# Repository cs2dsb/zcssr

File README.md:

# ZCSSR - Zero crossing solid state relay controller

A PCB and software for a SSR controller that monitors mains AC zero crossings to determine when to turn the SSR on.

[more images](docs/img)

## Why

I wanted to build a spot welder from an old MOT (microwave oven transformer) but wasn't satisfied with simply enabling the SSR at random because this makes the pulse +/- 1 half mains cycle (10ms on 50Hz, 8.3ms on 60Hz). It probably doesn't make much difference in the grand scheme of things but I wanted to know exactly how long the pulses were. 

This controller solves that issue by monitoring the mains zero crossing and triggering the SSR just before a zero crossing - the SSR has it's own zero crossing circuit to actually turn on it's output so as long as the controller doesn't fire more than 1 cycle early it will work as expected.

I also wanted to completely finish an embedded project written in rust and this project seemed about the right size undertaking.

## Uses

* Spot welder
* Reflow oven
* Sous vide
* Smoker
* Probably other things that need temp input (K-Type thermocouple) and switched mains ouput

## Features

* Zero crossing detection circuit
  * Pulse at least 0.4ms before the zero crossing
  * Isolated
  * 100-240V, 50/60Hz
  * [Details](docs/SimpleIsolatedZeroCrossDetector.pdf)
* UI
  * Quadrature encoder with push button 
  * LED for general status
  * LED for SSR status
  * 4 digit 14-segment LCD display. I2C
  * Trigger input 
* Temperature monitoring
  * NTC thermister for monitoring SSR/Transformer temperature
  * K-Type thermocouple input. MAX31855
* STM32F1 64-pin LQFP MCU. Specifically STM32F103RCT but any should work
* SWD (serial wire debug) programming & debugging
* USB hardware. In theory USB programming will be possible but not yet implemented

## Tools used

Not a complete list. Will add to it as features get implemented

* [Kicad](http://www.kicad.org/)
* [Rust](http://www.rust-lang.org/)
  * [cortex-m](http://github.com/rust-embedded/cortex-m) and [cortex-m-rt](http://github.com/rust-embedded/cortex-m-rt)
  * [cortex-m-rtfm RTOS](http://github.com/rtfm-rs/cortex-m-rtfm)
  * [stm32-rs peripheral register definitions](http://github.com/stm32-rs/stm32-rs)
  * [stm32f1xx-hal HAL implementation](http://github.com/stm32-rs/stm32f1xx-hal)
  * [adafruit-alphanum4.rs driver for Adafruit 14-segment LED Alphanumeric Backpack](http://github.com/cs2dsb/adafruit-alphanum4.rs)
    * [ht16k33 LED driver](http://github.com/jasonpeacock/ht16k33)

## Documentation

### Getting started

* Clone the repo
* Run `./bootstrap` script which will:
  * Initialize git submodules
  * Run `firmware/bootstrap` which will:
    * Checks if OS dependencies are installed
      * Currently `gcc`, `gdb`, `openocd` and `libudev-dev`
      * `sudo firmware/install_apt_deps` will install these deps if you are using a distribution that uses `apt`
    * Install or update rustup
    * Install required rust embedded toolchains
    * Install utils from crates.io
      * cargo-binutils
      * cargo-watch
      * llvm-tools-preview
      * serialitm
    * Run a cargo check, build and doc of the firmware (will take quite a while the first time)
* Direct flashing the the device
  * `firmware/deploy_standalone` will start openocd, flash the program and restart the device
* Debugging with gdb
  * `firmware/run_openocd` in one terminal
  * `firmware/release` or `firmware/debug` to build and launch gdb
  * Take a look at `firmware/openocd.gdb` and the scripts above to tweak the behaviour
* Log output
  * Firmware built with `--feature itm` will log over SWD
  * `firmware/monitor_itm` will launch `serialitm` to print this output with the ITM control characters stripped out. You may need to tweak the script if your uart dongle isn't `/dev/ttyUSB0`
* Tmux
  * `firmware/tmux_workspace` is a script that will open a tmux session with `firmware/run_openocd`, `firmware/monitor_itm` and `firmware/watch` in differnt panes to make development easy. Just type `./release` in one of the spare panes to deploy the software with gdb

### ITM logging

The code uses ITM logging to indicate start up progress and log info like temperatures and user config. If the ITM feature is enabled, the microcontroller won't run without openocd connected because there is some debug config openocd does to the chip that makes ITM work. I've added the obvious checks to the [itm_logger](https://github.com/cs2dsb/itm_logger.rs) crate but there's still something missing that I haven't got to the bottom of yet. There's [an issue](https://github.com/cs2dsb/itm_logger.rs/issues/1) to track it. The bottom line is if you want to be able to plug the hardware into the mains without OpenOCD connected you need to disable the `itm` feature (`firmware/deploy_standalone` already does this.)

### More info

Check [the docs folder](docs) for information on setting up the dev environment and various info on making the hardware.

## Mains warning

* Mains is dangerous, see the disclaimer
* A specific issue you might hit is powering the device over USB during development then plugging the mains in while the USB dongle is still attached. The mains will power the AC/DC on the board and that will backfeed 5v into the 3.3v/5v provided by the dongle. It's fine to leave the dongle connected if you disconnect it's 3.3v/5v line - only ground, swd, swclk should be connected to the ST-LINK if you want to plug the mains in. The UART connected to ground and swo is also fine. If you do backfeed 5v to the ST-LINK expect the ST-LINK to break as a minimum and the USB port it's connected to as a worst case. 

## Disclaimer

* This project uses mains electricity and will kill you if you handle it improperly
* You are responsible for your own safety
* Despite best efforts the author makes no guarantees that this design is safe, fit for purpose or meets any quality standards
* If you decide to build this or a similar device you must understand and take necessary safety precautions before proceeding
* The author cannot be held responsible for any damages or any form of loss that comes as a result of using any information found in this project

## License

This template is licensed under either of

- Apache License, Version 2.0 ([LICENSE-APACHE](LICENSE-APACHE) or
  http://www.apache.org/licenses/LICENSE-2.0)

- MIT license ([LICENSE-MIT](LICENSE-MIT) or http://opensource.org/licenses/MIT)

at your option.

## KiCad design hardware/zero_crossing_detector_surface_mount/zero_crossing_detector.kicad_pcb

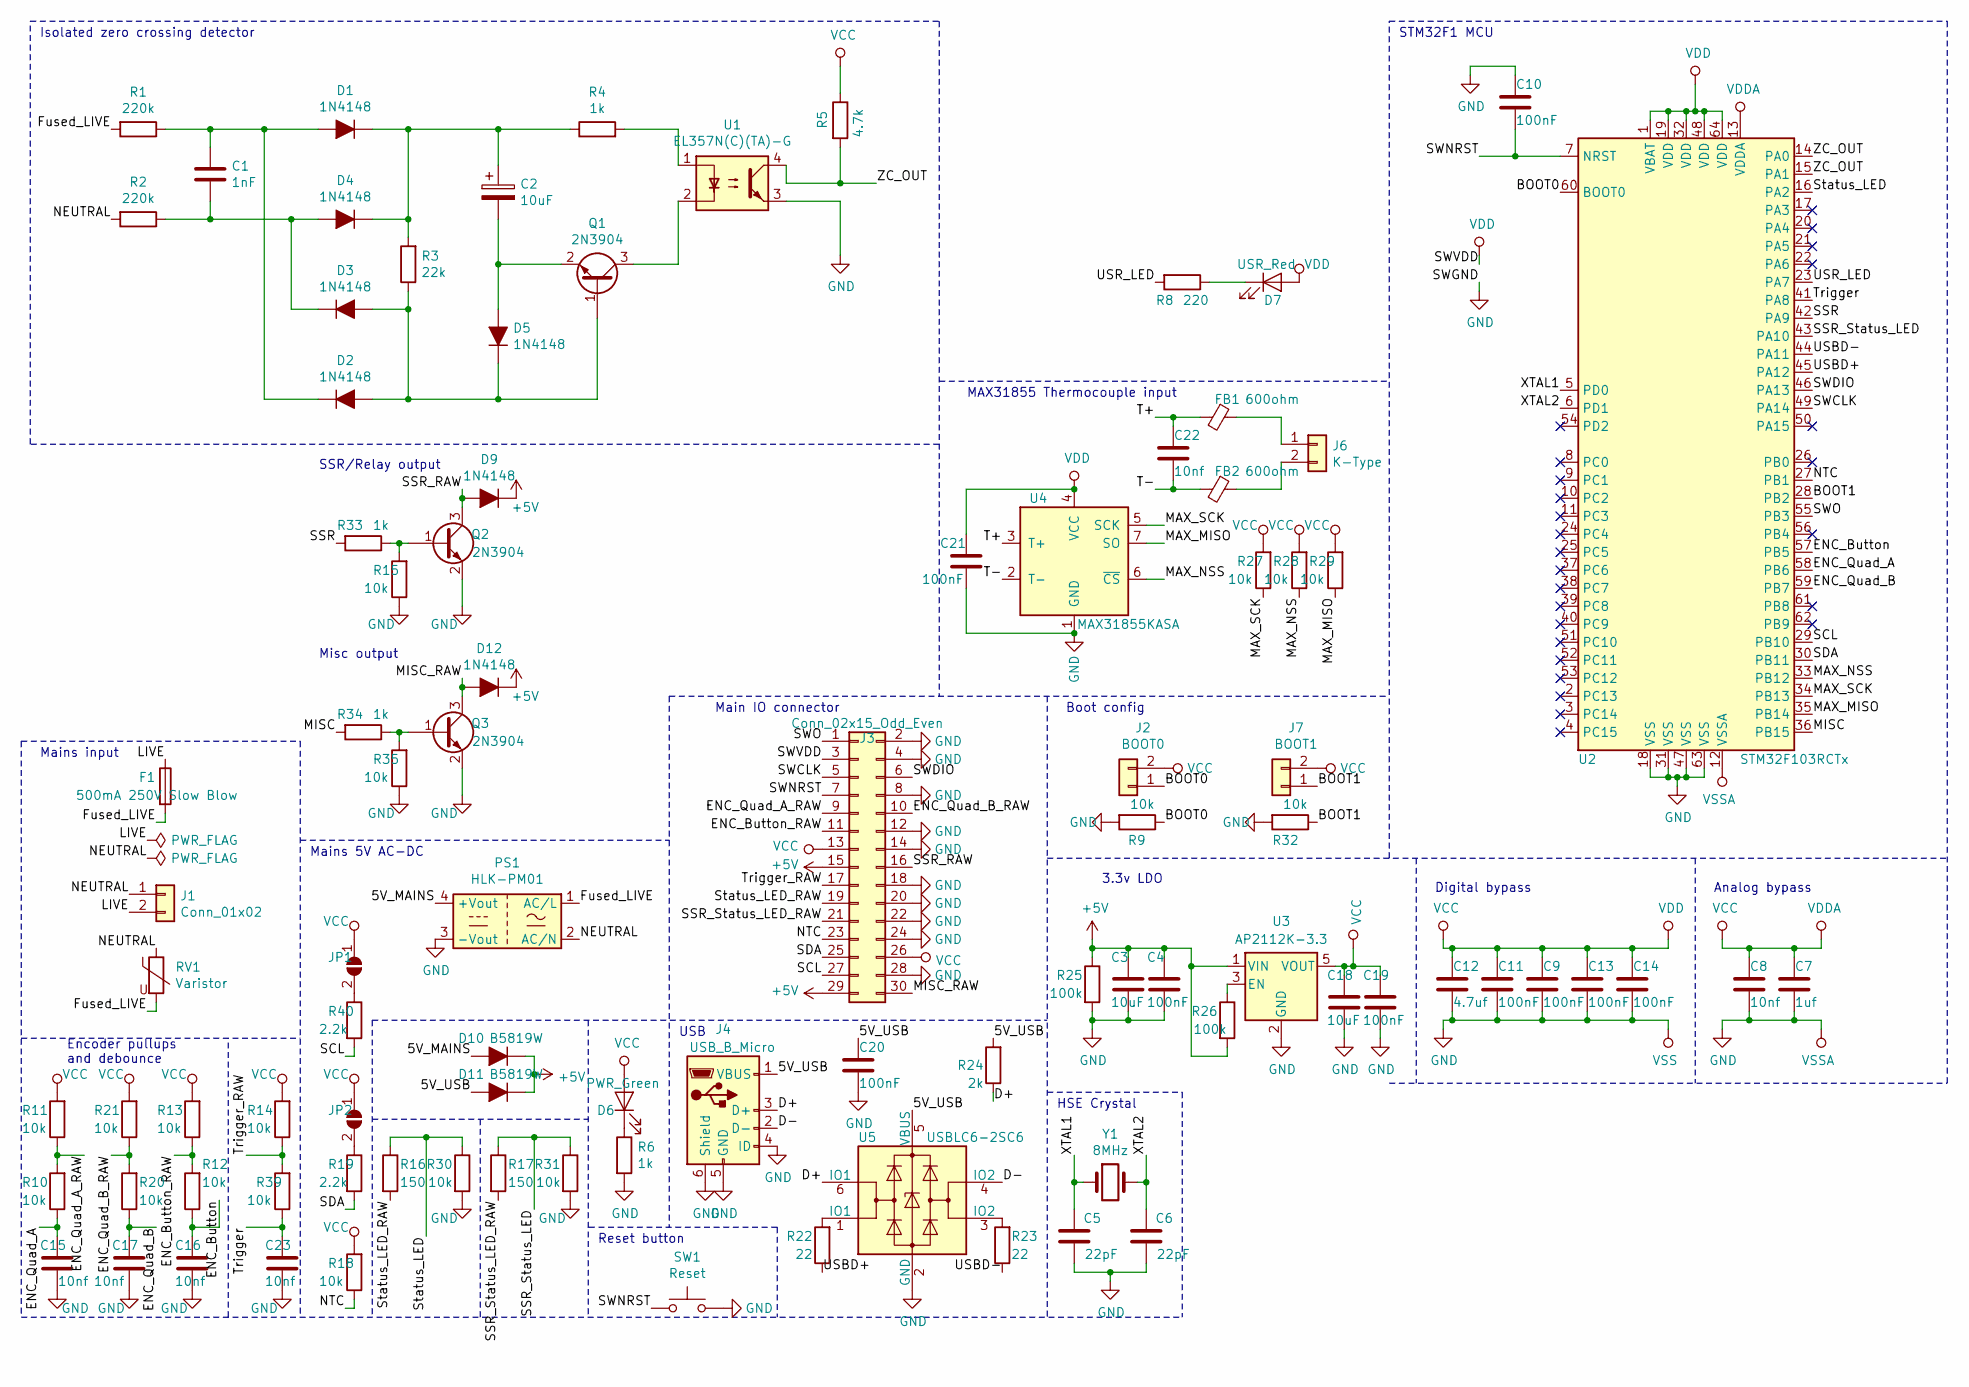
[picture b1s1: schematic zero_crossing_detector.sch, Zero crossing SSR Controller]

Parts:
C1: 1nF; C_0603_1608Metric; Part Number CL10B102KB8NNNC; LCSC Part Number C1588
C2: 10uF; C_0805_2012Metric; Part Number CL21A106KAYNNNE; LCSC Part Number C15850
C3, C18: 10uF; C_0402_1005Metric; Part Number CL05A106MQ5NUNC; LCSC Part Number C15525
C4, C9, C10, C11, C13, C14, C19, C20, C21: 100nF; C_0402_1005Metric; Part Number CL05B104KO5NNNC; LCSC Part Number C1525
C5, C6: 22pF; C_0402_1005Metric; Part Number 0402CG220J500NT; LCSC Part Number C1555
C7: 1uf; C_0402_1005Metric; Part Number CL05A105KA5NQNC; LCSC Part Number C52923
C8, C15, C16, C17, C22, C23: 10nf; C_0402_1005Metric; Part Number CL05B103KB5NNNC; LCSC Part Number C15195
C12: 4.7uf; C_0402_1005Metric; Part Number CL05A475MP5NRNC; LCSC Part Number C23733
D1, D2, D3, D4, D5, D9, D12: 1N4148; D_SOD-123; Part Number 1N4148W; LCSC Part Number C81598
D6: PWR_Green; LED_0603_1608Metric; Part Number 19-217/GHC-YR1S2/3T; LCSC Part Number C72043
D7: USR_Red; LED_0603_1608Metric; Part Number 红灯 0603; LCSC Part Number C2286
D10, D11: B5819W; D_SOD-123; Part Number B5819W; LCSC Part Number C8598
F1: 500mA 250V Slow Blow; Fuseholder_Cylinder-5x20mm_Stelvio-Kontek_PTF78_Horizontal_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; Part Number 64600001003,5T.0500240000R1D; LCSC Part Number C206887,C14050
FB1, FB2: 600ohm; L_0805_2012Metric; Part Number GZ2012D601TF; LCSC Part Number C1017
J1: Conn_01x02; Terminal_Block_Dinkle_EK508V_1x02_P5.08mm_Vertical; Part Number MKDS3/2-5.08; LCSC Part Number C89120
J2: BOOT0; PinHeader_1x02_P2.54mm_Vertical
J3: Conn_02x15_Odd_Even; PinHeader_2x15_P2.54mm_Vertical
J4: USB_B_Micro; ZX62M-B-5P(30)
J6: K-Type; PhoenixContact_MKDS_2-3.5; Part Number 1751248; LCSC Part Number C89122
J7: BOOT1; PinHeader_1x02_P2.54mm_Vertical
JP1, JP2: SolderJumper_2_Open; SolderJumper-2_P1.3mm_Open_TrianglePad1.0x1.5mm
PS1: HLK-PM01; Converter_ACDC_HiLink_HLK-PMxx; Part Number HLK-PM01; LCSC Part Number C209903
Q1, Q2, Q3: 2N3904; SOT-23; Part Number 2n3904S-RTK/P; LCSC Part Number C18536
R1, R2: 220k; R_0805_2012Metric; Part Number 0805W8F2203T5E; LCSC Part Number C17556
R3: 22k; R_0603_1608Metric; Part Number 0603WAF2202T5E; LCSC Part Number C31850
R4: 1k; R_0603_1608Metric; Part Number 0603WAF1001T5E; LCSC Part Number C21190
R5: 4.7k; R_0402_1005Metric; Part Number 0402WGF4701TCE; LCSC Part Number C25900
R6, R33, R34: 1k; R_0402_1005Metric; Part Number 0402WGF1001TCE; LCSC Part Number C11702
R8: 220; R_0402_1005Metric; Part Number 0402WGF2200TCE; LCSC Part Number C25091
R9, R10, R11, R12, R13, R14, R15, R18, R20, R21, R27, R28, R29, R30, R31, R32, R35, R39: 10k; R_0402_1005Metric; Part Number 0402WGF1002TCE; LCSC Part Number C25744
R16, R17: 150; R_0402_1005Metric; Part Number 0402WGF1500TCE; LCSC Part Number C25082
R19, R40: 2.2k; R_0402_1005Metric; Part Number 0402WGF2201TCE; LCSC Part Number C25879
R22, R23: 22; R_0402_1005Metric; Part Number 0402WGF220JTCE; LCSC Part Number C25092
R24: 2k; R_0402_1005Metric; Part Number 0402WGF2001TCE; LCSC Part Number C4109
R25, R26: 100k; R_0402_1005Metric; Part Number 0402WGF1003TCE; LCSC Part Number C25741
RV1: Varistor; RV_Disc_D12mm_W3.9mm_P7.5mm; Part Number 10D391K; LCSC Part Number C233184
SW1: Reset; SW_SPST_B3SL-1002P; Part Number TS-1187A-B-A-B; LCSC Part Number C318884
U1: EL357N(C)(TA)-G; SOP-4_3.8x4.1mm_P2.54mm; Part Number EL357N(C)(TA)-G; LCSC Part Number C29981
U2: STM32F103RCTx; LQFP-64_10x10mm_P0.5mm; Part Number STM32F103RCT6; LCSC Part Number C8323
U3: AP2112K-3.3; SOT-23-5; Part Number AP2112K-3.3TRG1; LCSC Part Number C51118
U4: MAX31855KASA; SOIC-8_3.9x4.9mm_P1.27mm
U5: USBLC6-2SC6; SOT-23-6; Part Number USBLC6-2SC6; LCSC Part Number C7519
Y1: 8MHz; Crystal_SMD_5032-2Pin_5.0x3.2mm; Part Number X50328MSB2GI; LCSC Part Number C115962

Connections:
+5V: C3.1, C4.1, D9.1 (K), D10.1 (K), D11.1 (K), D12.1 (K), J3.15, J3.29, R25.1, R26.2, U3.1 (VIN)
/5V_MAINS: D10.2 (A), PS1.4 (+Vout)
/5V_USB: C20.1, D11.2 (A), J4.1 (VBUS), R24.2, U5.5 (VBUS)
/BOOT0: J2.1, R9.1, U2.60 (BOOT0)
/BOOT1: J7.1, R32.1, U2.28 (PB2)
/D+: J4.3 (D+), R24.1, U5.6 (IO1)
/D-: J4.2 (D-), U5.4 (IO2)
/ENC_Button: C16.1, R12.1, U2.57 (PB5)
/ENC_Button_RAW: J3.11, R12.2, R13.1
/ENC_Quad_A: C15.1, R10.1, U2.58 (PB6)
/ENC_Quad_A_RAW: J3.9, R10.2, R11.1
/ENC_Quad_B: C17.1, R20.1, U2.59 (PB7)
/ENC_Quad_B_RAW: J3.10, R20.2, R21.1
/Fused_LIVE: F1.2, PS1.1 (AC/L), R1.2, RV1.2
/LIVE: F1.1, J1.2
/MAX_MISO: R29.1, U2.35 (PB14), U4.7 (SO)
/MAX_NSS: R28.1, U2.33 (PB12), U4.6 (~CS~)
/MAX_SCK: R27.1, U2.34 (PB13), U4.5 (SCK)
/MISC: R34.2, U2.36 (PB15)
/MISC_RAW: D12.2 (A), J3.30, Q3.3 (C)
/NEUTRAL: J1.1, PS1.2 (AC/N), R2.2, RV1.1
/NTC: J3.23, R18.1, U2.27 (PB1)
/SCL: J3.27, R40.2, U2.29 (PB10)
/SDA: J3.25, R19.2, U2.30 (PB11)
/SSR: R33.2, U2.42 (PA9)
/SSR_RAW: D9.2 (A), J3.16, Q2.3 (C)
/SSR_Status_LED: R17.1, R31.1, U2.43 (PA10)
/SSR_Status_LED_RAW: J3.21, R17.2
/SWCLK: J3.5, U2.49 (PA14)
/SWDIO: J3.6, U2.46 (PA13)
/SWNRST: C10.2, J3.7, SW1.1, U2.7 (NRST)
/SWO: J3.1, U2.55 (PB3)
/Status_LED: R16.1, R30.1, U2.16 (PA2)
/Status_LED_RAW: J3.19, R16.2
/T+: C22.1, FB1.2, U4.3 (T+)
/T-: C22.2, FB2.2, U4.2 (T-)
/Trigger: C23.1, R39.1, U2.41 (PA8)
/Trigger_RAW: J3.17, R14.1, R39.2
/USBD+: R22.1, U2.45 (PA12)
/USBD-: R23.1, U2.44 (PA11)
/USR_LED: R8.2, U2.23 (PA7)
/XTAL1: C5.2, U2.5 (PD0), Y1.1
/XTAL2: C6.2, U2.6 (PD1), Y1.2
/ZC_OUT: R5.2, U1.4, U2.14 (PA0), U2.15 (PA1)
GND: C3.2, C4.2, C5.1, C6.1, C7.2, C8.2, C9.2, C10.1, C11.2, C12.2, C13.2, C14.2, C15.2, C16.2, C17.2, C18.2, C19.2, C20.2, C21.2, C23.2, J3.2, J3.4, J3.8, J3.12, J3.14, J3.18, J3.20, J3.22, J3.24, J3.28, J4.4 (ID), J4.5 (GND), J4.6 (Shield), PS1.3 (-Vout), Q2.2 (E), Q3.2 (E), R6.2, R9.2, R15.1, R25.2, R30.2, R31.2, R32.2, R35.1, SW1.2, U1.3, U2.12 (VSSA), U2.18 (VSS), U2.31 (VSS), U2.47 (VSS), U2.63 (VSS), U3.2 (GND), U4.1 (GND), U5.2 (GND)
unnamed: C1.1, D1.2 (A), D2.1 (K), R1.1
unnamed: C1.2, D3.1 (K), D4.2 (A), R2.1
unnamed: C2.1, D1.1 (K), D4.1 (K), R3.2, R4.1
unnamed: C2.2, D5.2 (A), Q1.2 (E)
unnamed: D2.2 (A), D3.2 (A), D5.1 (K), Q1.1 (B), R3.1
unnamed: D6.1 (K), R6.1
unnamed: D7.1 (K), R8.1
unnamed: FB1.1, J6.1
unnamed: FB2.1, J6.2
unnamed: JP1.2 (B), R40.1
unnamed: JP2.2 (B), R19.1
unnamed: Q1.3 (C), U1.2
unnamed: Q2.1 (B), R15.2, R33.1
unnamed: Q3.1 (B), R34.1, R35.2
unnamed: R4.2, U1.1
unnamed: R22.2, U5.1 (IO1)
unnamed: R23.2, U5.3 (IO2)
unnamed: R26.1, U3.3 (EN)
VCC: C7.1, C8.1, C9.1, C11.1, C12.1, C13.1, C14.1, C18.1, C19.1, C21.1, D6.2 (A), D7.2 (A), J2.2, J3.3, J3.13, J3.26, J7.2, JP1.1 (A), JP2.1 (A), R5.1, R11.2, R13.2, R14.2, R18.2, R21.2, R27.2, R28.2, R29.2, U2.1 (VBAT), U2.13 (VDDA), U2.19 (VDD), U2.32 (VDD), U2.48 (VDD), U2.64 (VDD), U3.5 (VOUT), U4.4 (VCC)

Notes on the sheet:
Encoder pullups and debounce
Reset button
USB
HSE Crystal
STM32F1 MCU
Digital bypass
Analog bypass
3.3v LDO
Boot config
Main IO connector
Mains 5V AC-DC
Mains input
Isolated zero crossing detector
MAX31855 Thermocouple input
SSR/Relay output
Misc output

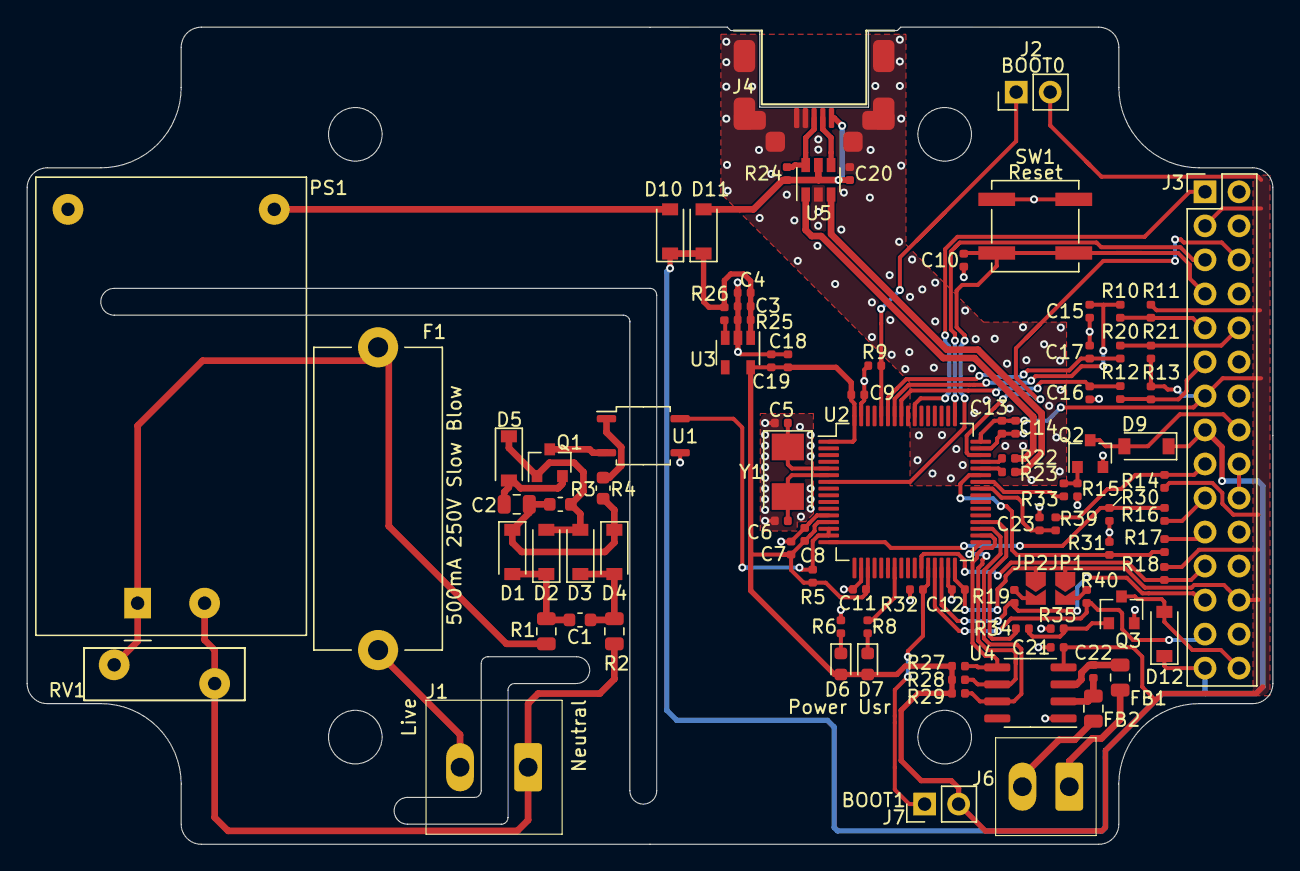
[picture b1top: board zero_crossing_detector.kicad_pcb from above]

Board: 2 copper layers, 93.0 x 61.0 mm, 93 parts (0 on the bottom side), 64 nets.

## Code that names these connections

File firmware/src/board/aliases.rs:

use stm32f1xx_hal::{
    gpio::{
        PushPull,
        Alternate,
        Input,
        Output,
        Floating,
        OpenDrain,
        Analog,
        gpioa::*,
        gpiob::*,
    },    
    timer::{
        Tim4NoRemap,
        CountDownTimer,
    },
    spi::{
        Spi,
        Spi2NoRemap,
        NoMosi,
    },
    i2c::BlockingI2c,
    pac::{
        I2C2,
        SPI2,
        TIM2,
        TIM4,
        TIM8,
        TIM1,
    },
    qei::Qei,
    pwm::{
        Pwm,
        C2,
        C3,
    },
};

#[cfg(not(feature = "dummy_zc"))]
use stm32f1xx_hal::{ 
    pwm_input::PwmInput,
    timer::Tim2NoRemap,
};
use ht16k33::HT16K33;

/// Zero crossing timer reads pwm input from the zero crossing detection circuit (or a dummy count down timer if dummy_zc feature is enabled)
pub type ZcTim = TIM2;
/// Quadrature encoder timer reads the quad input from the rotary encoder
pub type QuadTim = TIM4;
/// The UI timer provides a periodic interrupt to update the display, read temperature and periodically log useful info
pub type UiTim = TIM8;
/// The SSR timer drives the SsrEn pin to enable the welder. A timer is used so the control software crashing should never result in the SSR being left enabled
pub type SsrTim = TIM1;

/// The complete handle for the UI timer
pub type UiTimer = CountDownTimer<UiTim>;

/// Debug LED on PCB near MCU
/// TIM3_CH2
pub type LedUsr         = PA7<Output<PushPull>>;

/// Status LED to indicate ready, error, etc.
/// TIM5_CH3 (or TIM2_CH3)
pub type LedStatus      = PA2<Output<PushPull>>;

/// Status LED to indicate SSR status. Typically same state as SSR_EN
/// TIM1_CH3
pub type LedSsrStatus   = PA10<Alternate<PushPull>>;

/// Output that triggers SSR to allow current flow. Active high
/// TIM1_CH2
pub type SsrEn          = PA9<Alternate<PushPull>>;

/// Complete handle for the SSR output
pub type Ssr = (Pwm<SsrTim, C2>, Pwm<SsrTim, C3>);

/// Misc output (fans etc)
pub type MiscEn         = PB15<Output<PushPull>>;

/// Rotary encoder push button input. Active low
/// EXTI5
pub type EncBtn         = PB5<Input<Floating>>;

/// Rotary encoder quadrature input A
/// TIM4_CH1
pub type EncA           = PB6<Input<Floating>>;

/// Rotary encoder quadrature input B
/// TIM4_CH2
pub type EncB           = PB7<Input<Floating>>;

/// Complete handle for the encoder
pub type Encoder        = Qei<QuadTim, Tim4NoRemap, (EncA, EncB)>;

/// NTC thermister input. Half way point of resistor divider VCC-10k-\[NTC\]-GND
/// ADC1_CH9 (or ADC2_CH9)
pub type Ntc            = PB1<Analog>;

/// Input from zero crossing detection circuit. Active low
/// TIM2_CH1
pub type ZcRising       = PA0<Input<Floating>>;
/// Input from zero crossing detection circuit. Active low
/// TIM2_CH2
pub type ZcFalling      = PA1<Input<Floating>>;

#[cfg(not(feature = "dummy_zc"))] 
/// Complete handle for the Zc timer
pub type Zc = PwmInput<ZcTim, Tim2NoRemap, (ZcRising, ZcFalling)>;

#[cfg(feature = "dummy_zc")] 
/// Complete handle for the Zc timer
pub type Zc = CountDownTimer<ZcTim>;

/// User input trigger. Active low
/// EXTI8
pub type Trigger        = PA8<Input<Floating>>;

/// I2C clock for quad 14(?) segment display
/// I2C2
pub type DispScl        = PB10<Alternate<OpenDrain>>;

/// I2C data for quad 14(?) segment display
/// I2C2
pub type DispSda        = PB11<Alternate<OpenDrain>>;

/// The complete handle for the HT16K33 Display
pub type Display        = HT16K33<BlockingI2c<I2C2, (DispScl, DispSda)>>;

/// USB D-
pub type UsbDm<T>       = PA11<T>;

/// USB D+
pub type UsbDp<T>       = PA12<T>;

/// MAX31855K thermocouple converter - slave select, active low
/// Spi2
pub type KThermoNss     = PB12<Output<PushPull>>;

/// MAX31855K thermocouple converter - serial-clock
/// Spi2
pub type KThermoSck     = PB13<Alternate<PushPull>>;

/// MAX31855K thermocouple converter - serial data out
/// Spi2
pub type KThermoMiso    = PB14<Input<Floating>>;

/// Complete handle for the MAX31855 thermocouple
pub type Thermocouple = (Spi<SPI2, Spi2NoRemap, (KThermoSck, KThermoMiso, NoMosi)>, KThermoNss);

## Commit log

2019-11-11 Added some images of the boards
2019-11-11 Added v0.2 hardware files
2019-11-11 Documentation for sending PCB to JLCPCB and setting up the dev environment
2019-11-11 docs/README.md formatting
2019-11-11 Added open hardware logo to PCB. Fixed some doc typos
2019-11-11 Added project log
2019-11-13 Changed to 5v AC-DC module. Added transistor to drive SSR output. Updated LDO
2019-11-13 Updated smd_0.2_kicad.jpg
2019-11-14 Added some extra silkscreen labels to IO. Fixed image links in project log
2019-11-14 Updated parts list to match latest pcb changes
2019-11-14 Mostly functional 'UI' - pressing enc button cycles through, rotating changes the current setting. Encoder is a bit too sensitive for a single count to be a single step; this can be tweaked in code l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
2019-11-15 Added tiny 1x1mm RGB LED to pcb
2019-11-16 Switched USB ESD diode for STM recommened one. Added GND plane around USB traces on top layer
2019-11-16 Tweaked solder mask expansion
2019-11-16 Update project log
2019-11-19 Fixed rotation of U2
2019-11-21 Moved kicad custom footprints & components to a git submodule
2019-12-18 Rotated RGB led
2020-01-09 Reading from MAX31855 and some clean up in prep for new board
2020-01-14 All v0.2 hardware tested except USB. Uprevved hal version
2020-01-14 Uprevved cortex-m-rtfm to 0.5.0
2020-01-14 Fixed casing of resources to match rtfm 5 style
2020-01-18 ZC monitoring and SSR output on mains tested and working
2020-01-25 Refactored UI out of bin
2020-01-25 Added hw debouncing to trigger. Added SCL pull-up. Made both I2C pull-ups 2.2k and optional
2020-01-26 Split board.rs up into multiple files. Documentation. Moved most hardware config from bin to lib
2020-01-27 Switched to crates.io version of i2c_hung_fix and back to the github version of stm32f1xx-hal
2020-01-27 Moved ascii_str macro functionality into a proc macro in new macro_helpers lib. The new macro uses a typed transmute union with the correct number of characters on both sides to ensure there's no iss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
2020-01-28 Updated project log
2020-01-28 Shuffled board around to put AC/DC right on the edge so hopefully it will fit alongside an SSR mounted in the lid of the box
2020-01-29 Removed RGB led
2020-01-29 Switched to serialitm instead of hacky d2xx version. Updated docs
2021-11-08 Update README.md
    https://forum.kicad.info/t/warning-avoid-all-links-to-kicad-pcb-org-use-kicad-org/31521
